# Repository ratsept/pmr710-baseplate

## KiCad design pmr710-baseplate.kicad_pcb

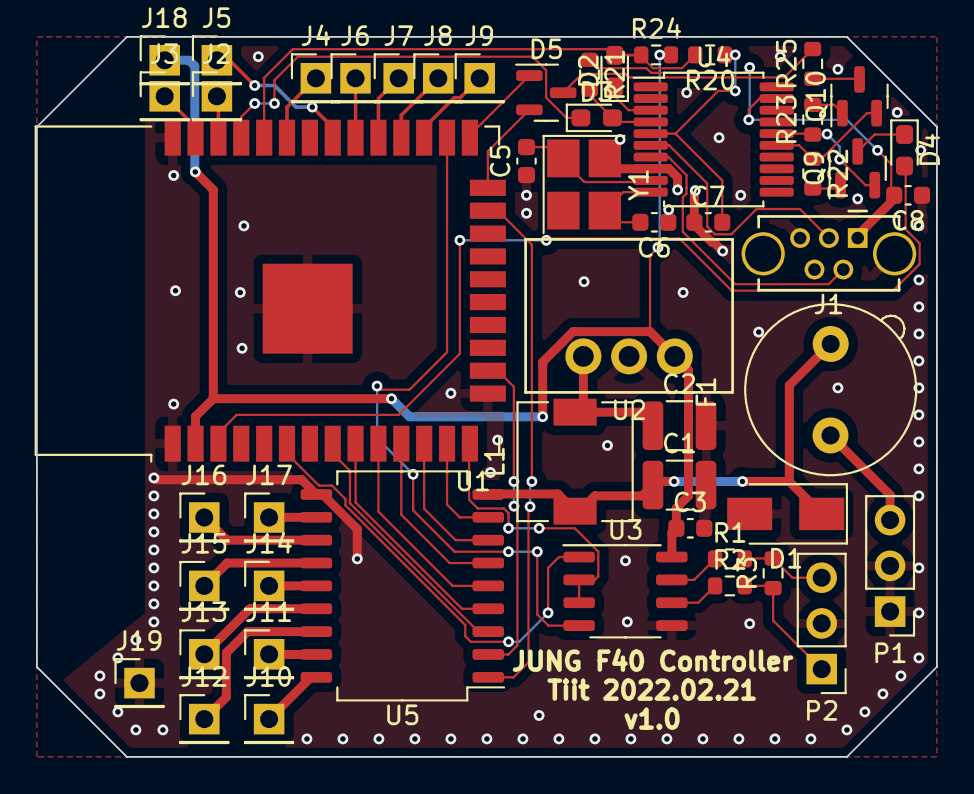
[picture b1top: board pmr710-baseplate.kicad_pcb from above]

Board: 2 copper layers, 50.0 x 40.0 mm, 52 parts (0 on the bottom side), 56 nets.

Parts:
C1, C2: 10u 50V; C_1210_3225Metric
C3, C7: 100n; C_0603_1608Metric
C5, C6: 20p; C_0603_1608Metric
C8: 22u; C_0603_1608Metric
D1: D_Schottky_Small; D_SMA
D2, D3, D4: D_Schottky_Small; D_0603_1608Metric_Pad1.05x0.95mm_HandSolder
D5: BAT54C; SOT-23
F1: F_Small; Fuseholder_TR5_Littelfuse_No560_No460
J1: USB_B_Micro; USB_Mini-B_Tensility_54-00023_Vertical_CircularHoles
J2, J3, J4, J5, J6, J7, J8, J9, J10, J11, J12, J13, J14, J15, J16, J17, J18, J19: Conn_01x01; PinHeader_1x01_P2.54mm_Vertical
L1: 68u; L_6.3x6.3_H3
P1: PWR; PinHeader_1x03_P2.54mm_Vertical
P2: RS485; PinHeader_1x03_P2.54mm_Vertical
Q9, Q10: BC817; SOT-23
R1, R2: 100R; R_0603_1608Metric
R3, R24: DNP; R_0603_1608Metric
R20, R21: 10k; R_0603_1608Metric
R22, R23: 1k; R_0603_1608Metric
R25: 220R; R_0603_1608Metric
U1: ESP32-WROOM-32
U2: R-78E-1.0
U3: MAX481E; SO-8_3.9x4.9mm_P1.27mm
U4: CH340T; SSOP-20_5.3x7.2mm_P0.65mm
U5: TBD62783A; SOP-18_7x12.5mm_P1.27mm
Y1: Crystal_GND24_Small; Crystal_SMD_3225-4Pin_3.2x2.5mm_HandSoldering

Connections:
+3V3: C3.1, J18.1, R24.2, U1.2 (VDD), U2.3 (VOUT), U3.8 (VCC)
+5V: C8.2, J1.1 (VBUS), R21.1, U4.19 (VCC)
+24V: C1.1, D1.1 (K), F1.2, L1.1, U5.9 (VCC)
BUT_0: J2.1, U1.36 (IO22)
BUT_1: J3.1, U1.37 (IO23)
BUT_2: J4.1, U1.33 (IO21)
BUT_3: J5.1, U1.31 (IO19)
BUT_4: J6.1, U1.30 (IO18)
BUT_5: J7.1, U1.29 (IO5)
BUT_6: J8.1, U1.28 (IO17)
BUT_7: J9.1, U1.27 (IO16)
DI: U1.26 (IO4), U3.4 (DI)
ESP_EN: D4.2 (A), U1.3 (EN)
GND: C1.2, C2.2, C3.2, C5.1, C6.1, C7.1, C8.1, D1.2 (A), J1.5 (GND), J1.6 (Shield), J19.1, P1.1, P1.2, P2.2, U1.1 (GND), U1.15 (GND), U1.38 (GND), U1.39 (GND), U2.2 (GND), U3.5 (GND), U4.8 (GND), U5.10 (GND), Y1.4
GPIO_0: D5.1, U1.25 (IO0)
GPIO_2: D5.2, U1.24 (IO2)
LED_0: U1.23 (IO15), U5.1 (I1)
LED_1: U1.16 (IO13), U5.2 (I2)
LED_2: U1.8 (IO32), U5.3 (I3)
LED_3: U1.9 (IO33), U5.4 (I4)
LED_4: U1.10 (IO25), U5.5 (I5)
LED_5: U1.11 (IO26), U5.6 (I6)
LED_6: U1.12 (IO27), U5.7 (I7)
LED_7: U1.13 (IO14), U5.8 (I8)
unnamed: C2.1, L1.2, U2.1 (VIN)
unnamed: C5.2, U4.9 (XI), Y1.1
unnamed: C6.2, U4.10 (XO), Y1.3
unnamed: C7.2, R20.1, U4.5 (V3)
unnamed: D2.1 (K), U4.3 (TXD)
unnamed: D3.2 (A), R21.2, U4.4 (RXD)
unnamed: D4.1 (K), Q9.3 (C)
unnamed: D5.3, R25.2
unnamed: F1.1, P1.3
unnamed: J1.2 (D-), U4.7 (UD-)
unnamed: J1.3 (D+), U4.6 (UD+)
unnamed: P2.1, R2.2, R3.1
unnamed: P2.3, R1.2, R3.2
unnamed: Q9.1 (B), R22.2
unnamed: Q9.2 (E), R23.1, U4.16 (~RTS)
unnamed: Q10.1 (B), R23.2
unnamed: Q10.2 (E), R22.1, U4.15 (~DTR)
unnamed: Q10.3 (C), R25.1
unnamed: R1.1, U3.7 (B)
unnamed: R2.1, U3.6 (A)
unnamed: J17.1, U5.11 (O8)
unnamed: J16.1, U5.12 (O7)
unnamed: J15.1, U5.13 (O6)
unnamed: J14.1, U5.14 (O5)
unnamed: J13.1, U5.15 (O4)
unnamed: J12.1, U5.16 (O3)
unnamed: J11.1, U5.17 (O2)
unnamed: J10.1, U5.18 (O1)
RO: U1.6 (IO34), U3.1 (RO)
RXD_0: D2.2 (A), R20.2, R24.1, U1.34 (RXD0/IO3)
TXD_0: D3.1 (K), U1.35 (TXD0/IO1)
~RXTX: U1.14 (IO12), U3.2 (~RE), U3.3 (DE)

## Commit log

2022-02-21 first gerbers generated
2022-02-21 generated gerber archive
